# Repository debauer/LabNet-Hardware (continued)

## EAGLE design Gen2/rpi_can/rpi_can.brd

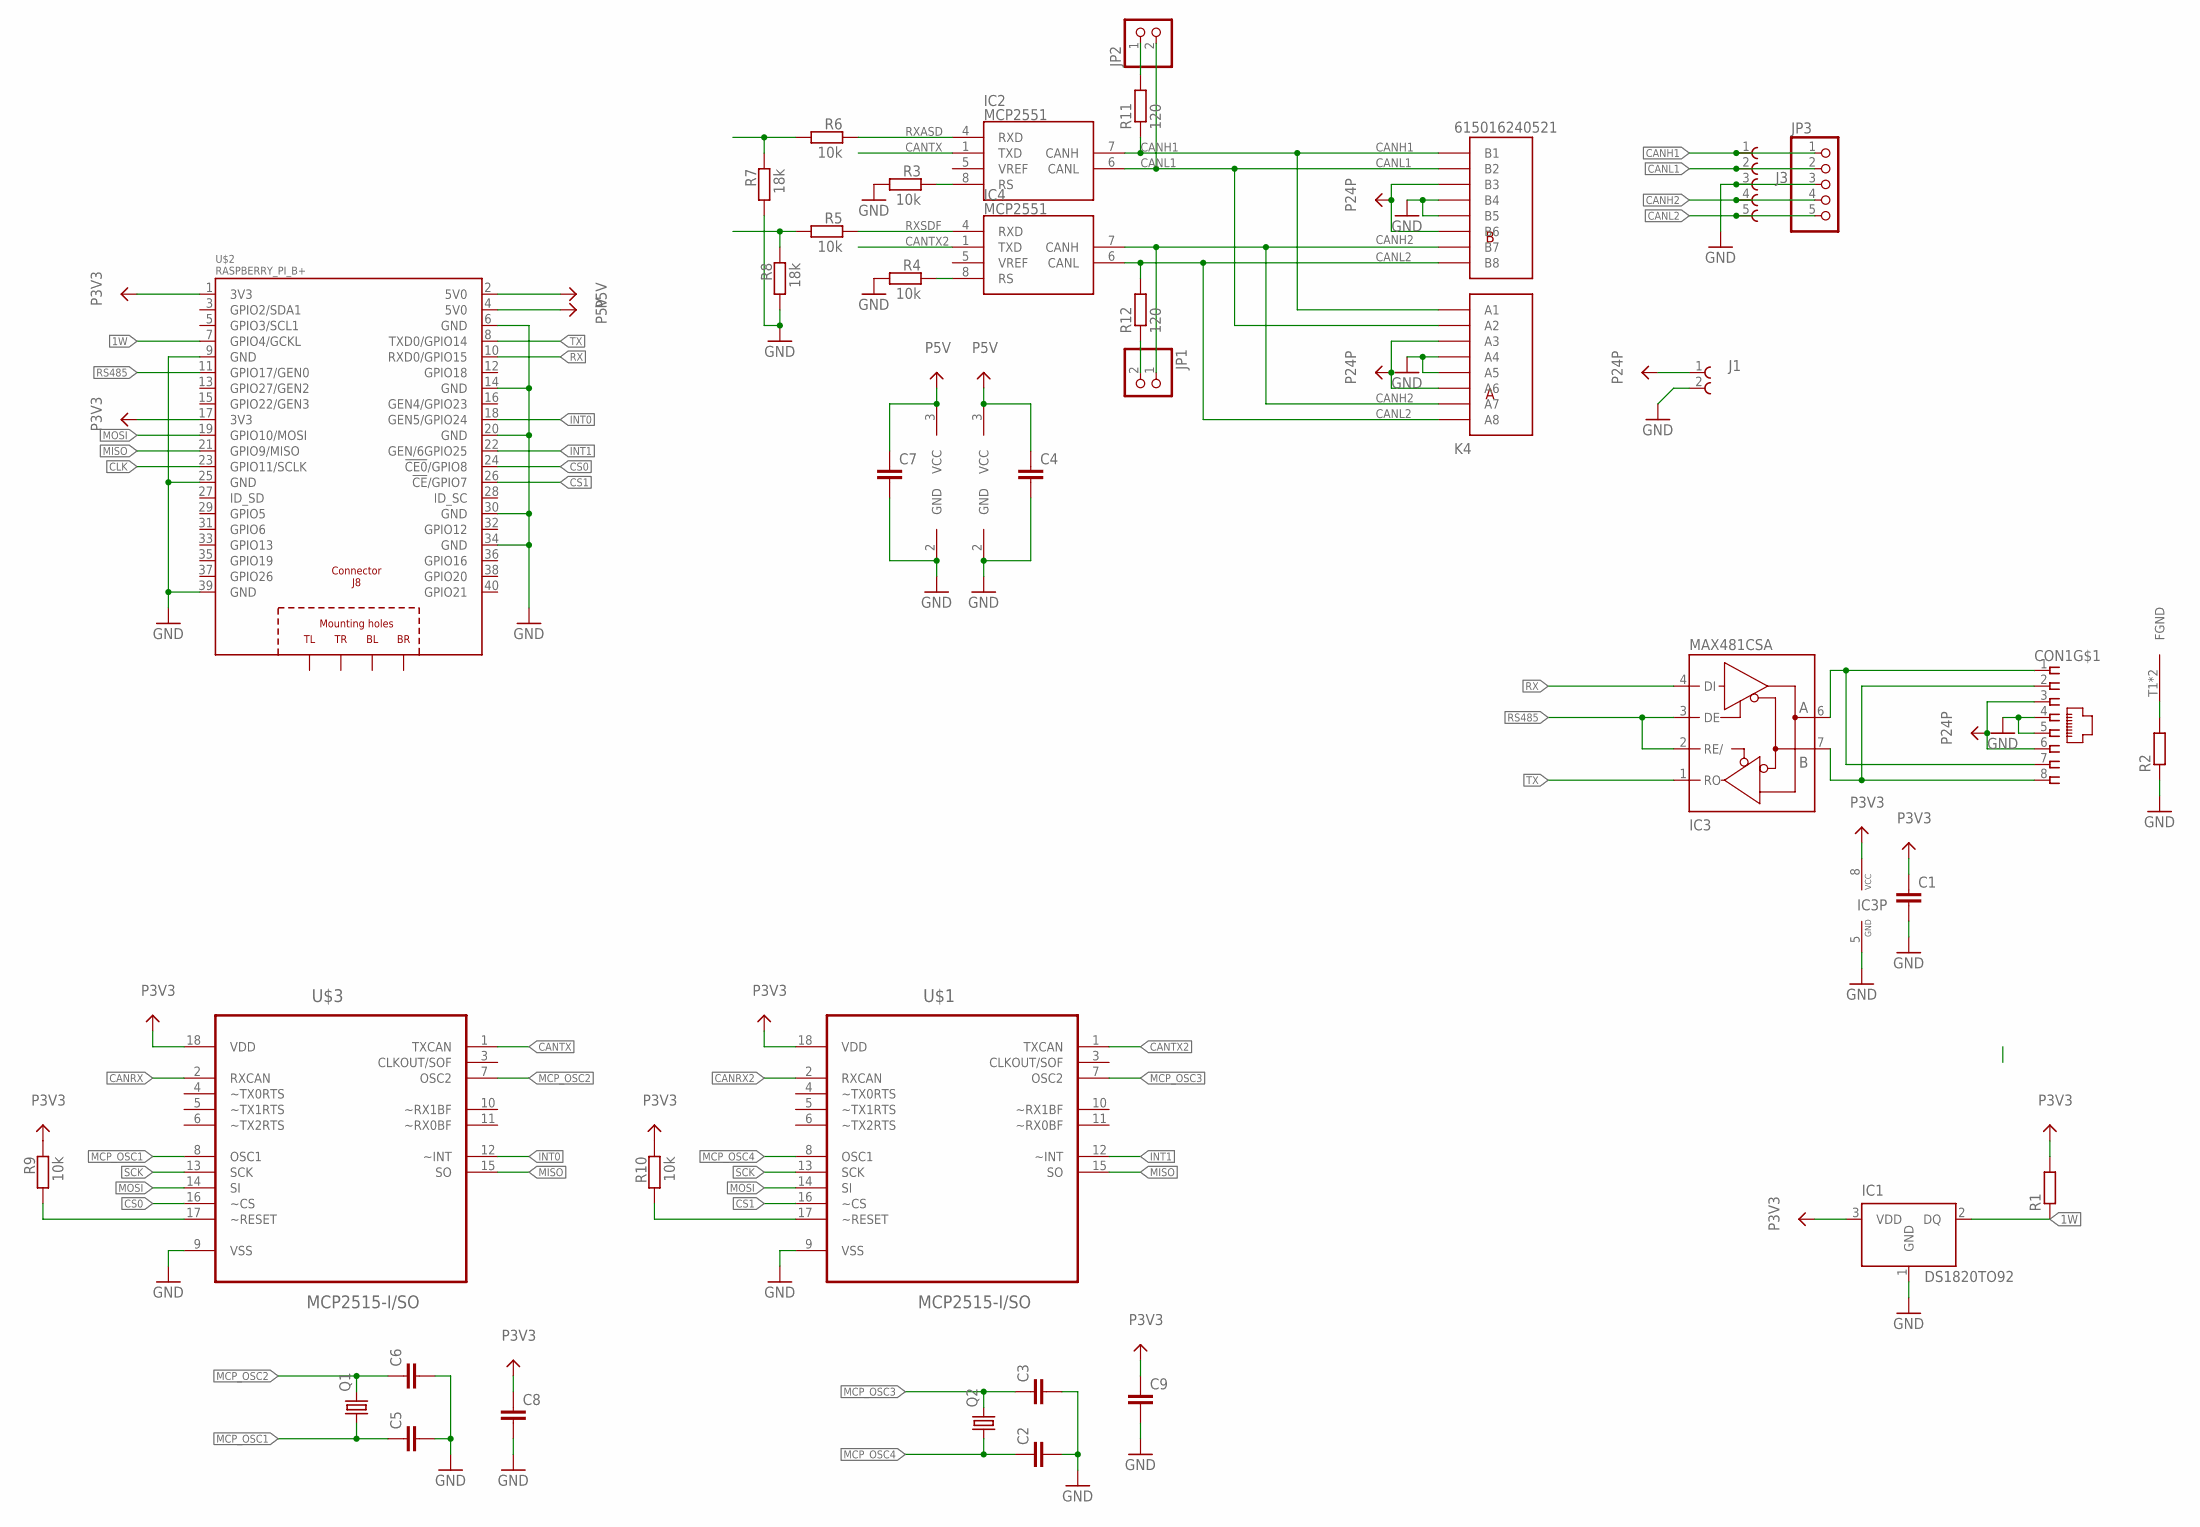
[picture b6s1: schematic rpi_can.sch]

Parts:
C1, C2, C3, C4, C5, C6, C7, C8, C9: C-EUC0805; C0805
CON1: MEBP_8-8G; MEBP
IC1: DS1820TO92; TO-92
IC2, IC4: MCP2551; SO-8
IC3: MAX481CSA; SO08
J1: 691322310002
J3: 691322310005
JP1, JP2: PINHD-1X2; 1X02
JP3: PINHD-1X5; 1X05
K4: 615016240521
Q1, Q2: CRYSTALHC49S; HC49/S
R1, R2: R-EU_R0805; R0805
R3, R4, R5, R6, R9, R10: 10k; R0805
R7, R8: 18k; R0805
R11, R12: 120; R0805
U$1, U$3: MCP2515-I/SO; SOIC127P1034X264-18N
U$2: RASPBERRY_PI_B+

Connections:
1W: IC1.2 (DQ), R1.1, U$2.7 (GPIO4/GCKL)
CANH1: IC2.7 (CANH), J3.1, JP3.1, K4.A1, K4.B1, R11.1
CANH2: IC4.7 (CANH), J3.4, JP1.1, JP3.4, K4.A7, K4.B7
CANL1: IC2.6 (CANL), J3.2, JP2.2, JP3.2, K4.A2, K4.B2
CANL2: IC4.6 (CANL), J3.5, JP3.5, K4.A8, K4.B8, R12.2
CANRX: R6.2, R7.1, U$3.2 (RXCAN)
CANRX2: R5.2, R8.1, U$1.2 (RXCAN)
CANTX: IC2.1 (TXD), U$3.1 (TXCAN)
CANTX2: IC4.1 (TXD), U$1.1 (TXCAN)
CLK: U$2.23 (GPIO11/SCLK)
CS0: U$2.24 (!CE0!/GPIO8), U$3.16 (~CS)
CS1: U$1.16 (~CS), U$2.26 (!CE!/GPIO7)
GND: C1.2, C2.2, C3.2, C4.2, C5.2, C6.2, C7.2, C8.2, C9.2, CON1.4, CON1.5, IC1.1 (GND), IC2.2 (GND), IC3.5 (GND), IC4.2 (GND), J1.2, J3.3, JP3.3, K4.A4, K4.A5, K4.B4, K4.B5, R2.1, R3.2, R4.2, R7.2, R8.2, U$1.9 (VSS), U$2.6 (GND), U$2.9 (GND), U$2.14 (GND), U$2.20 (GND), U$2.25 (GND), U$2.30 (GND), U$2.34 (GND), U$2.39 (GND), U$3.9 (VSS)
INT0: U$2.18 (GEN5/GPIO24), U$3.12 (~INT)
INT1: U$1.12 (~INT), U$2.22 (GEN/6GPIO25)
MCP_OSC1: C5.1, Q1.1, U$3.8 (OSC1)
MCP_OSC2: C6.1, Q1.2, U$3.7 (OSC2)
MCP_OSC3: C3.1, Q2.2, U$1.7 (OSC2)
MCP_OSC4: C2.1, Q2.1, U$1.8 (OSC1)
MISO: U$1.15 (SO), U$2.21 (GPIO9/MISO), U$3.15 (SO)
MOSI: U$1.14 (SI), U$2.19 (GPIO10/MOSI), U$3.14 (SI)
unnamed: R10.2, U$1.17 (~RESET)
unnamed: IC2.8 (RS), R3.1
unnamed: CON1.T1 (FGND), CON1.T2 (FGND), R2.2
unnamed: IC4.8 (RS), R4.1
unnamed: R9.2, U$3.17 (~RESET)
unnamed: JP2.1, R11.2
unnamed: JP1.2, R12.1
P3V3: C1.1, C8.1, C9.1, IC1.3 (VDD), IC3.8 (VCC), R1.2, R9.1, R10.1, U$1.18 (VDD), U$2.1 (3V3), U$2.17 (3V3), U$3.18 (VDD)
P5V: C4.1, C7.1, IC2.3 (VCC), IC4.3 (VCC), U$2.2 (5V0), U$2.4 (5V0)
P24P: CON1.3, CON1.6, J1.1, K4.A3, K4.A6, K4.B3, K4.B6
RS485: IC3.2 (RE/), IC3.3 (DE), U$2.11 (GPIO17/GEN0)
RS485_A: CON1.1, CON1.7, IC3.6 (A)
RS485_B: CON1.2, CON1.8, IC3.7 (B)
RX: IC3.4 (DI), U$2.10 (RXD0/GPIO15)
RXASD: IC2.4 (RXD), R6.1
RXSDF: IC4.4 (RXD), R5.1
SCK: U$1.13 (SCK), U$3.13 (SCK)
TX: IC3.1 (RO), U$2.8 (TXD0/GPIO14)

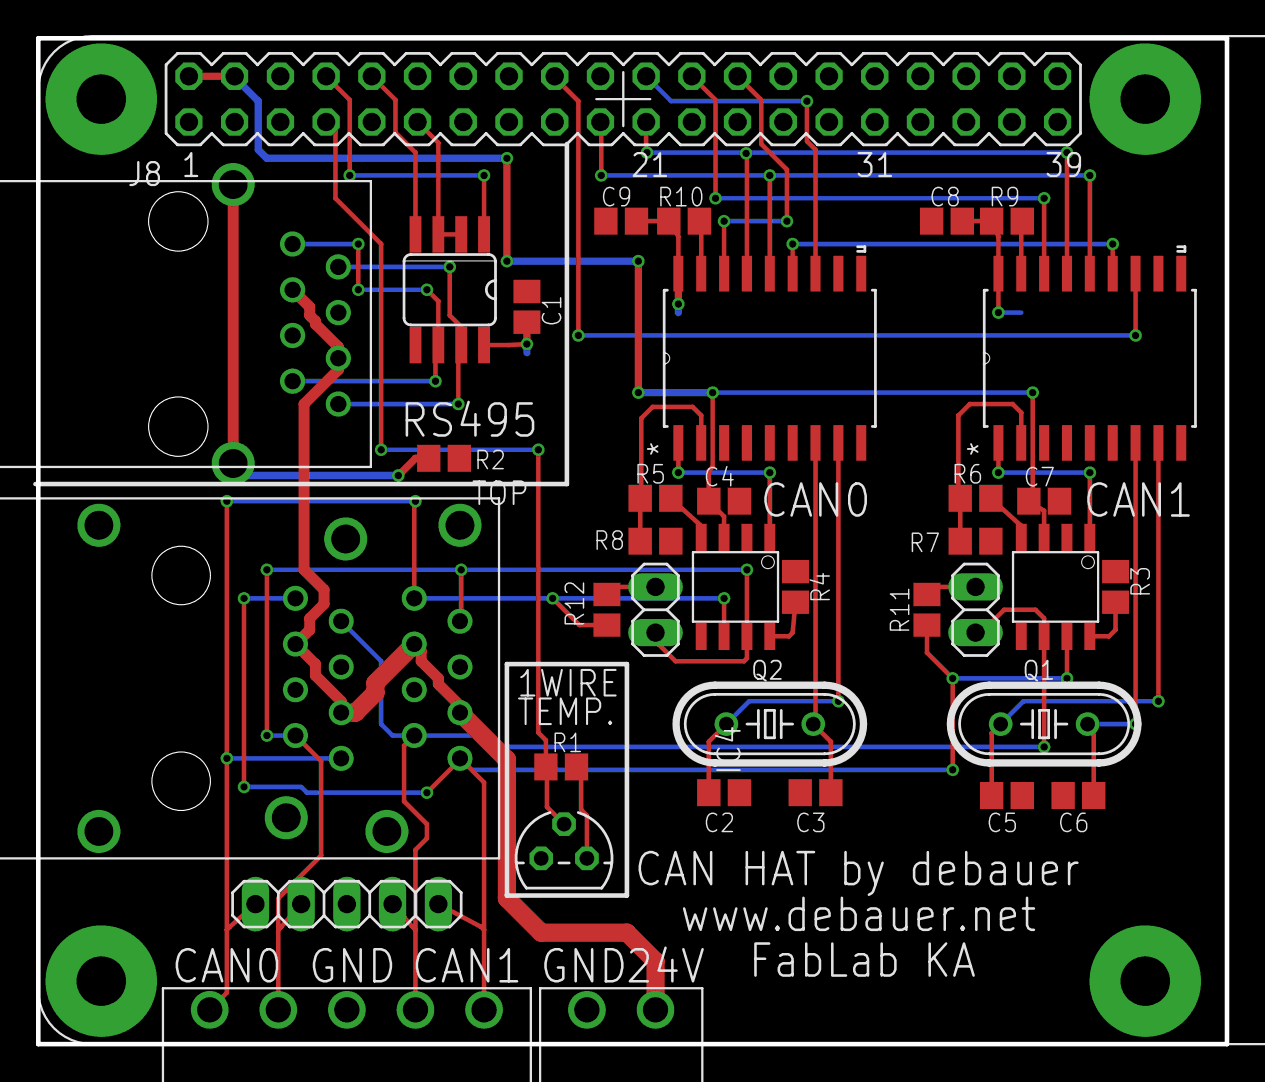
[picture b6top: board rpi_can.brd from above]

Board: 2 copper layers, 66.0 x 55.9 mm, 37 parts (0 on the bottom side), 38 nets.

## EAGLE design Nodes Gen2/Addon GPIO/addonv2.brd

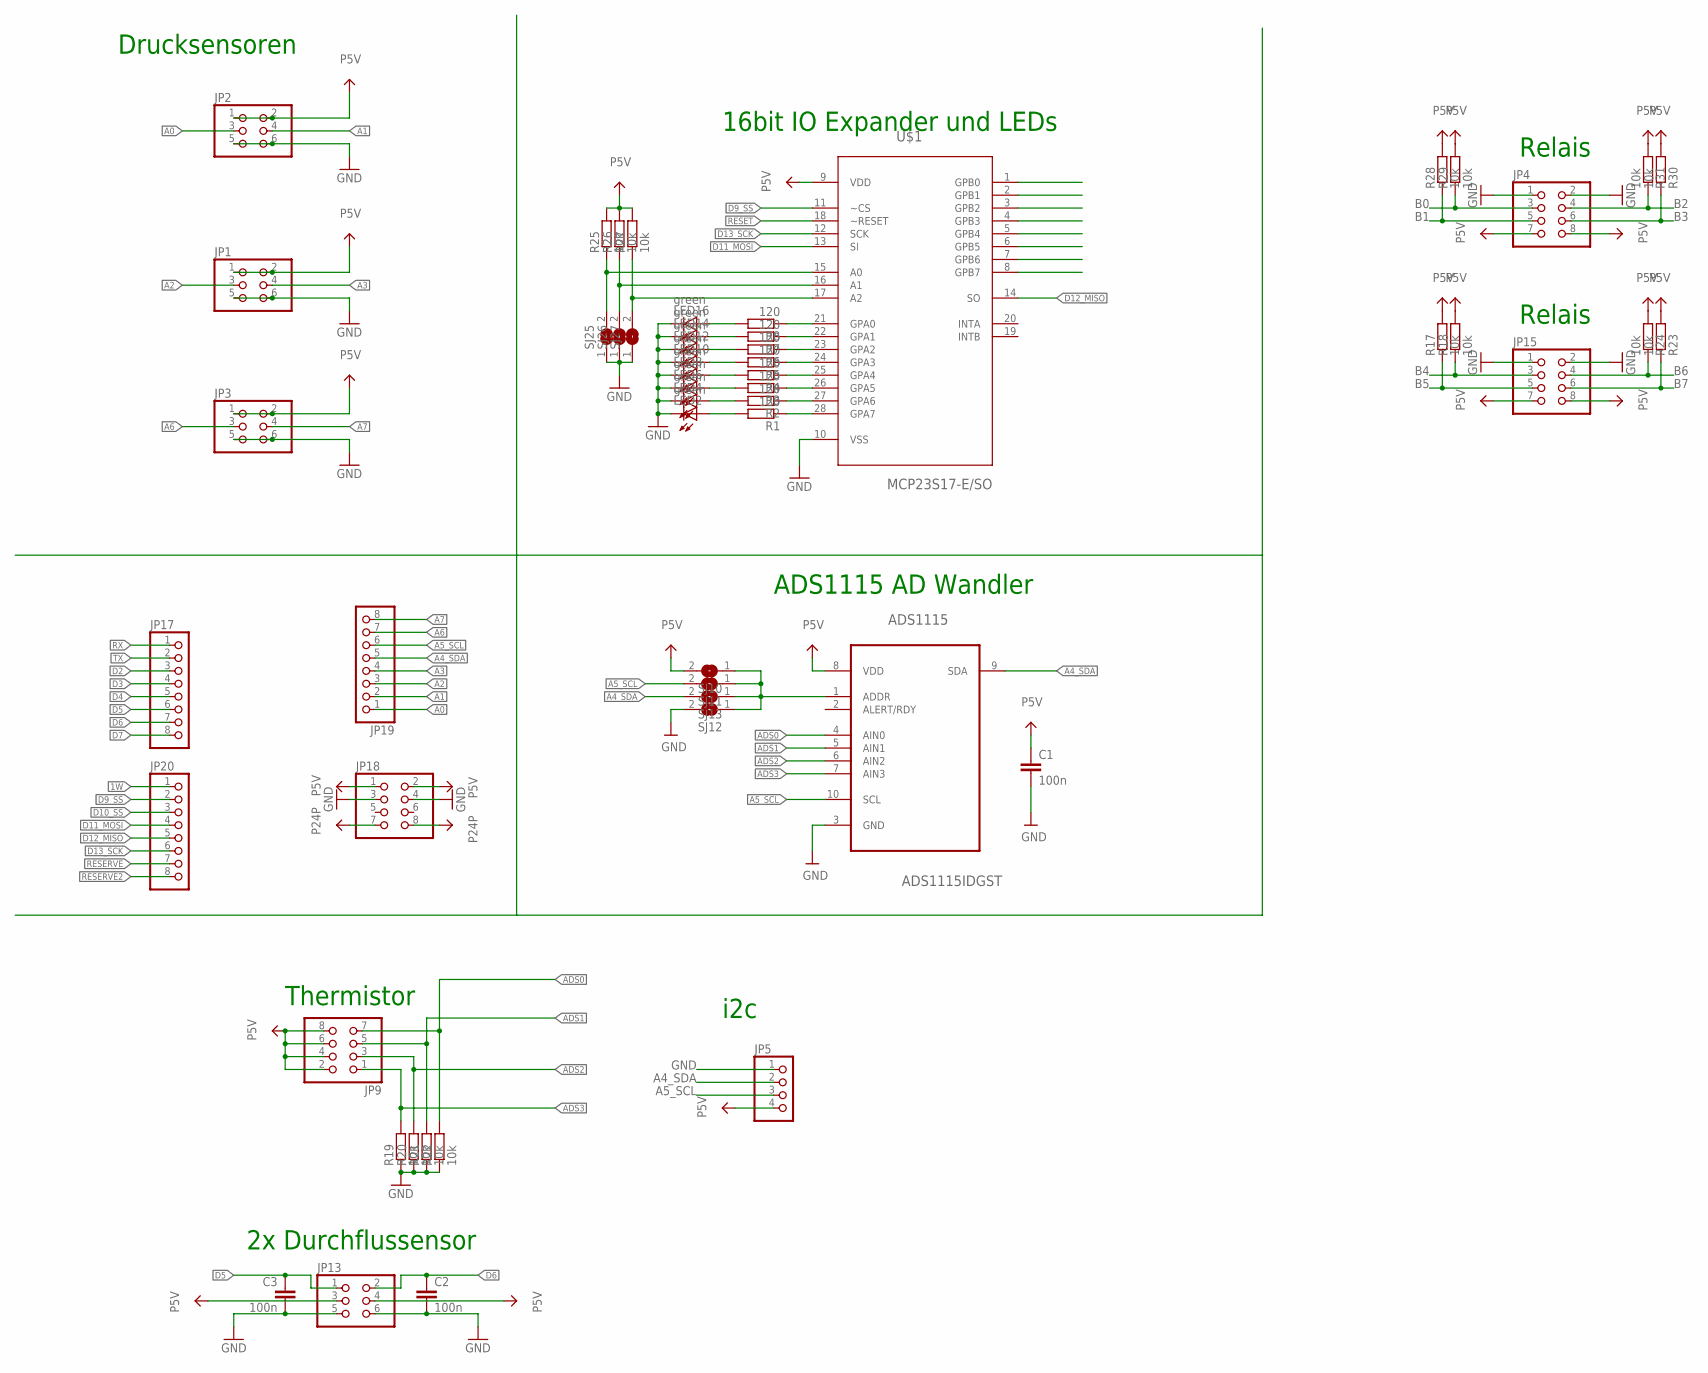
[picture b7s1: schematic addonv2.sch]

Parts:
ADS1115: ADS1115IDGST; SOP50P490X110-10N
C1, C2, C3: 100n; C0805
JP1, JP2, JP3, JP13: PINHD-2X3/90; 2X03/90
JP4, JP9, JP15: PINHD-2X4/90; 2X04/90
JP5: PINHD-1X4/90; 1X04/90
JP17, JP19, JP20: PINHD-1X8; 1X08
JP18: PINHD-2X4; 2X04
LED2, LED4, LED6, LED8, LED10, LED12, LED14, LED16: green; CHIPLED_0805
R1, R2, R3, R4, R5, R6, R7, R8: 120; R0603
R17, R18, R19, R20, R21, R22, R23, R24, R25, R26, R27, R28, R29, R30, R31: 10k; R0603
SJ10, SJ11, SJ12, SJ13, SJ25, SJ26, SJ27: SJN; SJ
U$1: MCP23S17-E/SO; SOIC127P030X265-28N

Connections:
1W: JP20.1
A0: JP2.3, JP19.1
A1: JP2.4, JP19.2
A2: JP1.3, JP19.3
A3: JP1.4, JP19.4
A4_SDA: ADS1115.9 (SDA), JP5.2, JP19.5, SJ13.2
A5_SCL: ADS1115.10 (SCL), JP5.3, JP19.6, SJ11.2
A6: JP3.3, JP19.7
A7: JP3.4, JP19.8
ADS0: ADS1115.4 (AIN0), JP9.7, R22.2
ADS1: ADS1115.5 (AIN1), JP9.5, R21.2
ADS2: ADS1115.6 (AIN2), JP9.3, R20.2
ADS3: ADS1115.7 (AIN3), JP9.1, R19.2
B0: JP4.3, R29.1, U$1.1 (GPB0)
B1: JP4.5, R28.1, U$1.2 (GPB1)
B2: JP4.4, R31.1, U$1.3 (GPB2)
B3: JP4.6, R30.1, U$1.4 (GPB3)
B4: JP15.3, R18.1, U$1.5 (GPB4)
B5: JP15.5, R17.1, U$1.6 (GPB5)
B6: JP15.4, R24.1, U$1.7 (GPB6)
B7: JP15.6, R23.1, U$1.8 (GPB7)
D2: JP17.3
D3: JP17.4
D4: JP17.5
D5: C3.1, JP13.1, JP17.6
D6: C2.1, JP13.2, JP17.7
D7: JP17.8
D9_SS: JP20.2, U$1.11 (~CS)
D10_SS: JP20.3
D11_MOSI: JP20.4, U$1.13 (SI)
D12_MISO: JP20.5, U$1.14 (SO)
D13_SCK: JP20.6, U$1.12 (SCK)
GND: ADS1115.3 (GND), C1.2, C2.2, C3.2, JP1.5, JP1.6, JP2.5, JP2.6, JP3.5, JP3.6, JP4.1, JP4.2, JP5.1, JP13.5, JP13.6, JP15.1, JP15.2, JP18.3, JP18.4, LED2.C, LED4.C, LED6.C, LED8.C, LED10.C, LED12.C, LED14.C, LED16.C, R19.1, R20.1, R21.1, R22.1, SJ12.2, SJ25.1, SJ26.1, SJ27.1, U$1.10 (VSS)
unnamed: LED2.A, R1.2
unnamed: LED4.A, R2.2
unnamed: LED6.A, R3.2
unnamed: LED8.A, R4.2
unnamed: LED10.A, R5.2
unnamed: LED12.A, R6.2
unnamed: LED14.A, R7.2
unnamed: LED16.A, R8.2
unnamed: R1.1, U$1.28 (GPA7)
unnamed: R2.1, U$1.27 (GPA6)
unnamed: R3.1, U$1.26 (GPA5)
unnamed: R4.1, U$1.25 (GPA4)
unnamed: R5.1, U$1.24 (GPA3)
unnamed: R6.1, U$1.23 (GPA2)
unnamed: R7.1, U$1.22 (GPA1)
unnamed: R8.1, U$1.21 (GPA0)
unnamed: ADS1115.1 (ADDR), SJ10.1, SJ11.1, SJ12.1, SJ13.1
unnamed: R25.1, SJ25.2, U$1.15 (A0)
unnamed: R26.1, SJ26.2, U$1.16 (A1)
unnamed: R27.1, SJ27.2, U$1.17 (A2)
P5V: ADS1115.8 (VDD), C1.1, JP1.1, JP1.2, JP2.1, JP2.2, JP3.1, JP3.2, JP4.7, JP4.8, JP5.4, JP9.2, JP9.4, JP9.6, JP9.8, JP13.3, JP13.4, JP15.7, JP15.8, JP18.1, JP18.2, R17.2, R18.2, R23.2, R24.2, R25.2, R26.2, R27.2, R28.2, R29.2, R30.2, R31.2, SJ10.2, U$1.9 (VDD)
P24P: JP18.7, JP18.8
RESERVE: JP20.7
RESERVE2: JP20.8
RESET: U$1.18 (~RESET)
RX: JP17.1
TX: JP17.2

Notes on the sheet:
2x Durchflussensor
Relais
Thermistor
i2c
16bit IO Expander und LEDs
Drucksensoren
ADS1115 AD Wandler

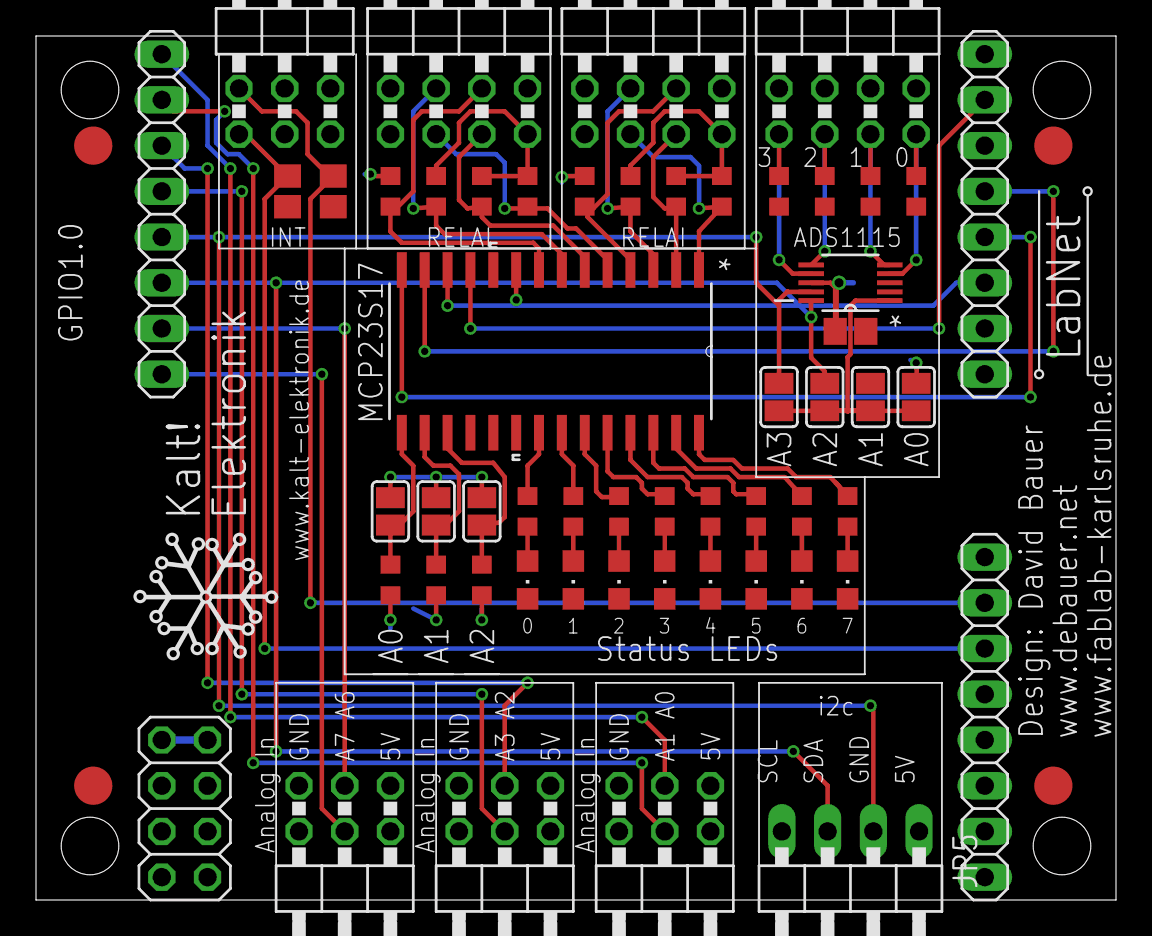
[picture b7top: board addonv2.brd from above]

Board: 2 copper layers, 60.0 x 48.0 mm, 61 parts (0 on the bottom side), 49 nets.

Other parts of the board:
U$2: KALT!ELEKTRONIK
U$3, U$4, U$5, U$7: PASSMARK
U$8: LABNET
